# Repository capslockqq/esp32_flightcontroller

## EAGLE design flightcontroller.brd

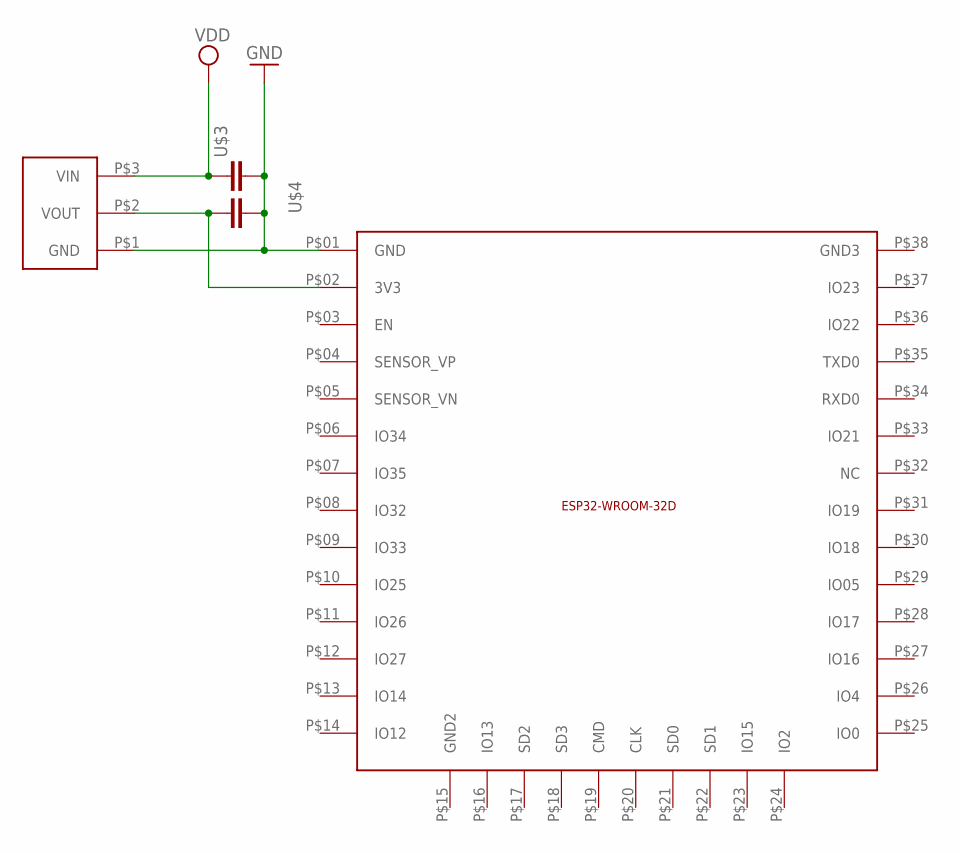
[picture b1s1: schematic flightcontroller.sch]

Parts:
U$1: ESP32; ESP32-WROOM-32D
U$2: REG1117
U$3, U$4: C_TANTALUM-1411(3528-METRIC); CAPM3528X210

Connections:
GND: U$1.P$01 (GND), U$2.P$1 (GND), U$3.2, U$4.2
unnamed: U$1.P$02 (3V3), U$2.P$2 (VOUT), U$4.1
VDD: U$2.P$3 (VIN), U$3.1

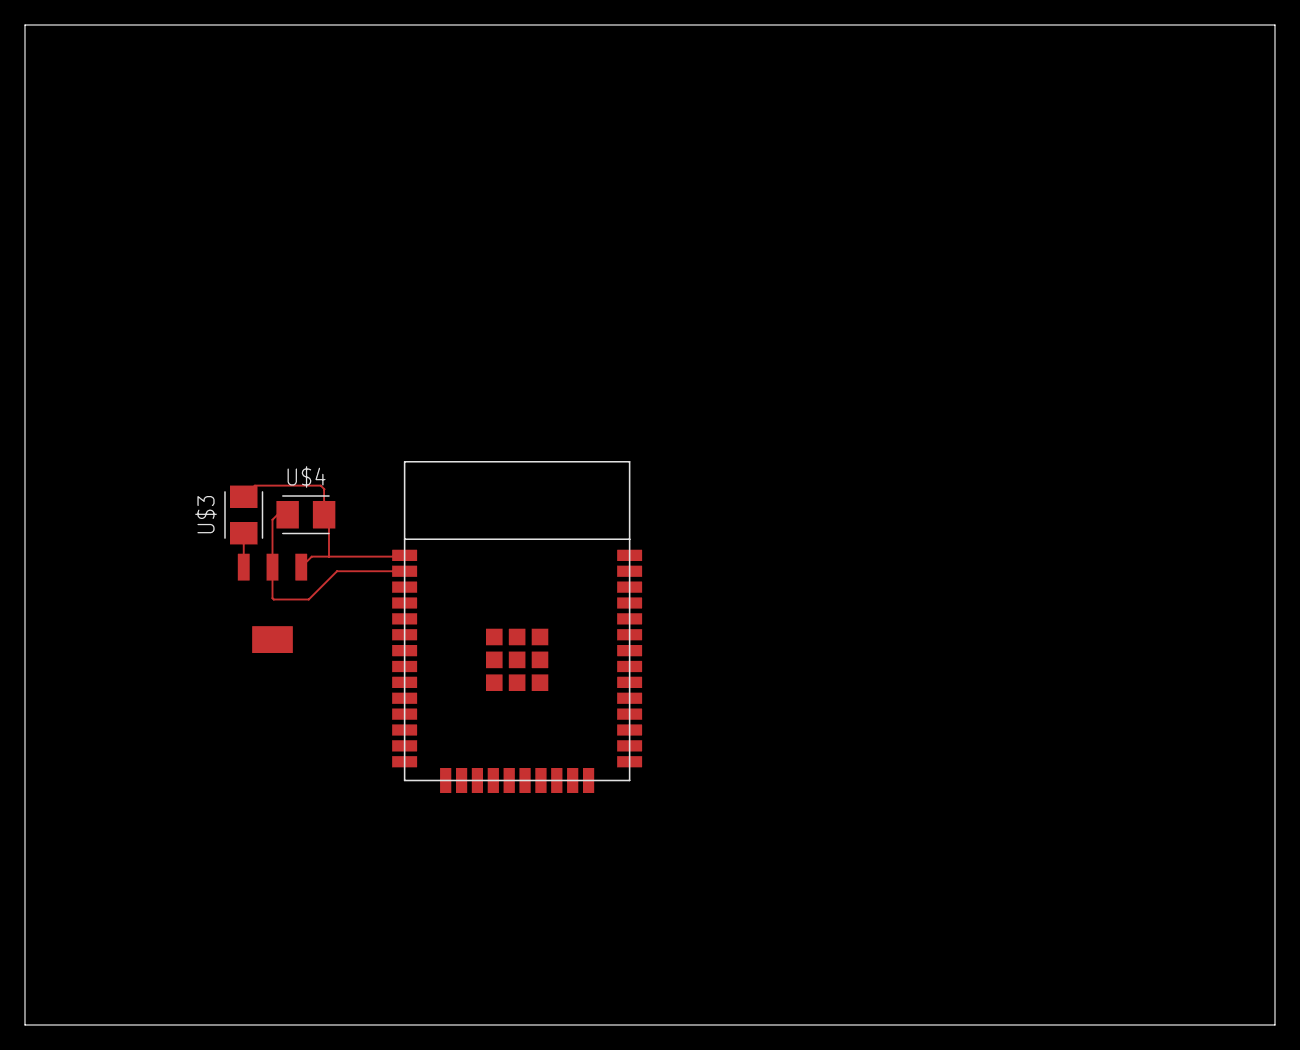
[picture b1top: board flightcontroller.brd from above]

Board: 2 copper layers, 100.0 x 80.0 mm, 4 parts (0 on the bottom side), 3 nets.

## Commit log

2020-02-09 initail
